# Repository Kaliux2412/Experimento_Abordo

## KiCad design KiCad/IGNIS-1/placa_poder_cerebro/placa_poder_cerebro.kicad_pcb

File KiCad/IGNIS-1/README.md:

# IGNIS-1 — estructura KiCad

## Fuente canónica = `boards/`

El diseño real y la fabricación viven en **3 proyectos KiCad independientes**:

- `boards/cerebro/` — power + MCU (ESP32, buck-boost 3V3, batería/RBF/switch)
- `boards/sensores/` — sensores + boost 5V (BME280, MPU6050, MQ-135, GPS)
- `boards/rf/` — comms + storage (LoRa RFM95W, microSD)

Cada uno es `*.kicad_pro` con su `*.kicad_sch` + `*.kicad_pcb`. **Abrir cada proyecto por separado** para editar/rutear. Se conectan por backplane 2×10 (J40/J41/J42, pinout idéntico).

## `IGNIS-1.kicad_sch` = NO CANÓNICO

El jerárquico raíz (`IGNIS-1.kicad_sch` + `sheets/*.kicad_sch`) es solo **referencia integrada histórica** previa al split en 3 placas. **NO refleja** los cambios hechos después en `boards/`:

- footprints `*_HandSolder` (C/R/LED SMD),
- caps bulk polarizados THT (`C_Polarized`: C2, C10, C32, C4),
- eliminación de U1 (protección 1S incluida en la celda LiPo) + re-cableado de la batería.

No editar ni fabricar desde el jerárquico.

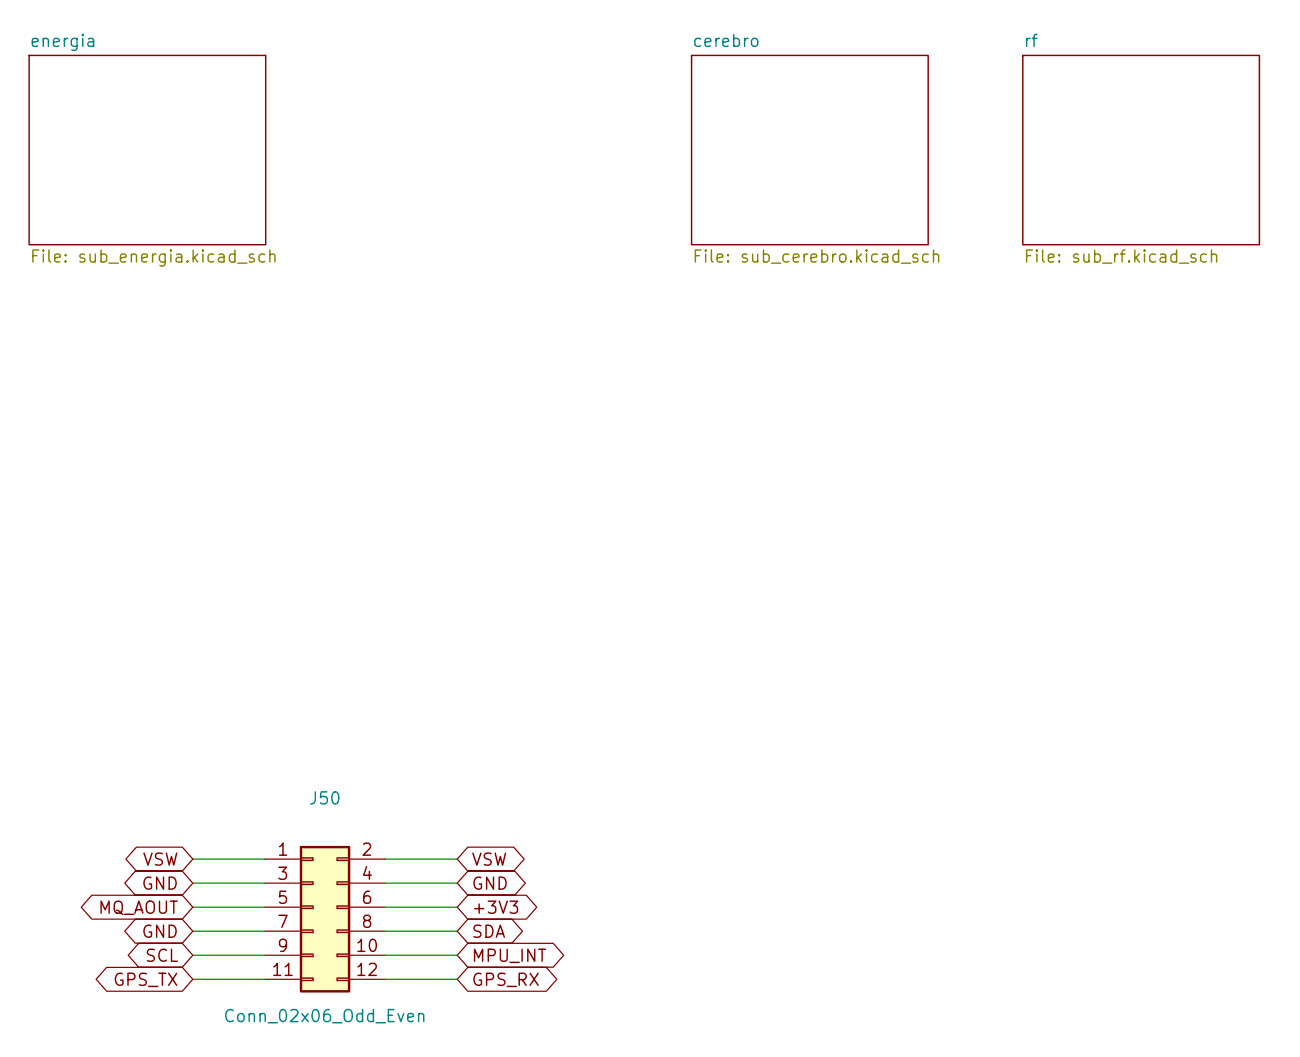
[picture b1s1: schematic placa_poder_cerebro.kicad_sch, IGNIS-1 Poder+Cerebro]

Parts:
J50: Conn_02x06_Odd_Even; PinHeader_2x06_P2.54mm_Vertical

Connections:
+3V3: J50.6; also elsewhere on the board
GND: J50.3, J50.4, J50.7; also elsewhere on the board
GPS_RX: J50.12; also elsewhere on the board
GPS_TX: J50.11; also elsewhere on the board
MPU_INT: J50.10; also elsewhere on the board
MQ_AOUT: J50.5; also elsewhere on the board
SCL: J50.9; also elsewhere on the board
SDA: J50.8; also elsewhere on the board
VSW: J50.1, J50.2; also elsewhere on the board

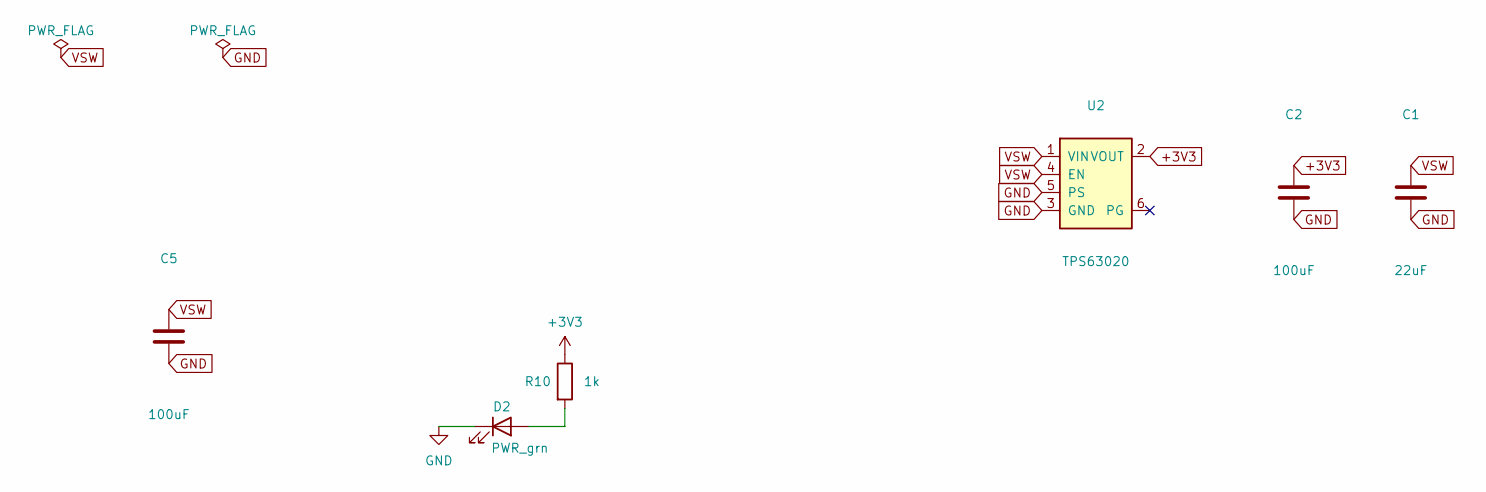
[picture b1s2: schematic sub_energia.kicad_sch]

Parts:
C1: 22uF; C_1206_3216Metric
C2, C5: 100uF; C_1210_3225Metric
D2: PWR_grn; LED_D3.0mm
R10: 1k; R_0805_2012Metric
U2: TPS63020; TPS63020_module

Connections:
+3V3: C2.1, R10.1, U2.2 (VOUT); also elsewhere on the board
GND: C1.2, C2.2, C5.2, D2.1 (K), U2.3 (GND), U2.5 (PS); also elsewhere on the board
unnamed: D2.2 (A), R10.2
VSW: C1.1, C5.1, U2.1 (VIN), U2.4 (EN); also elsewhere on the board

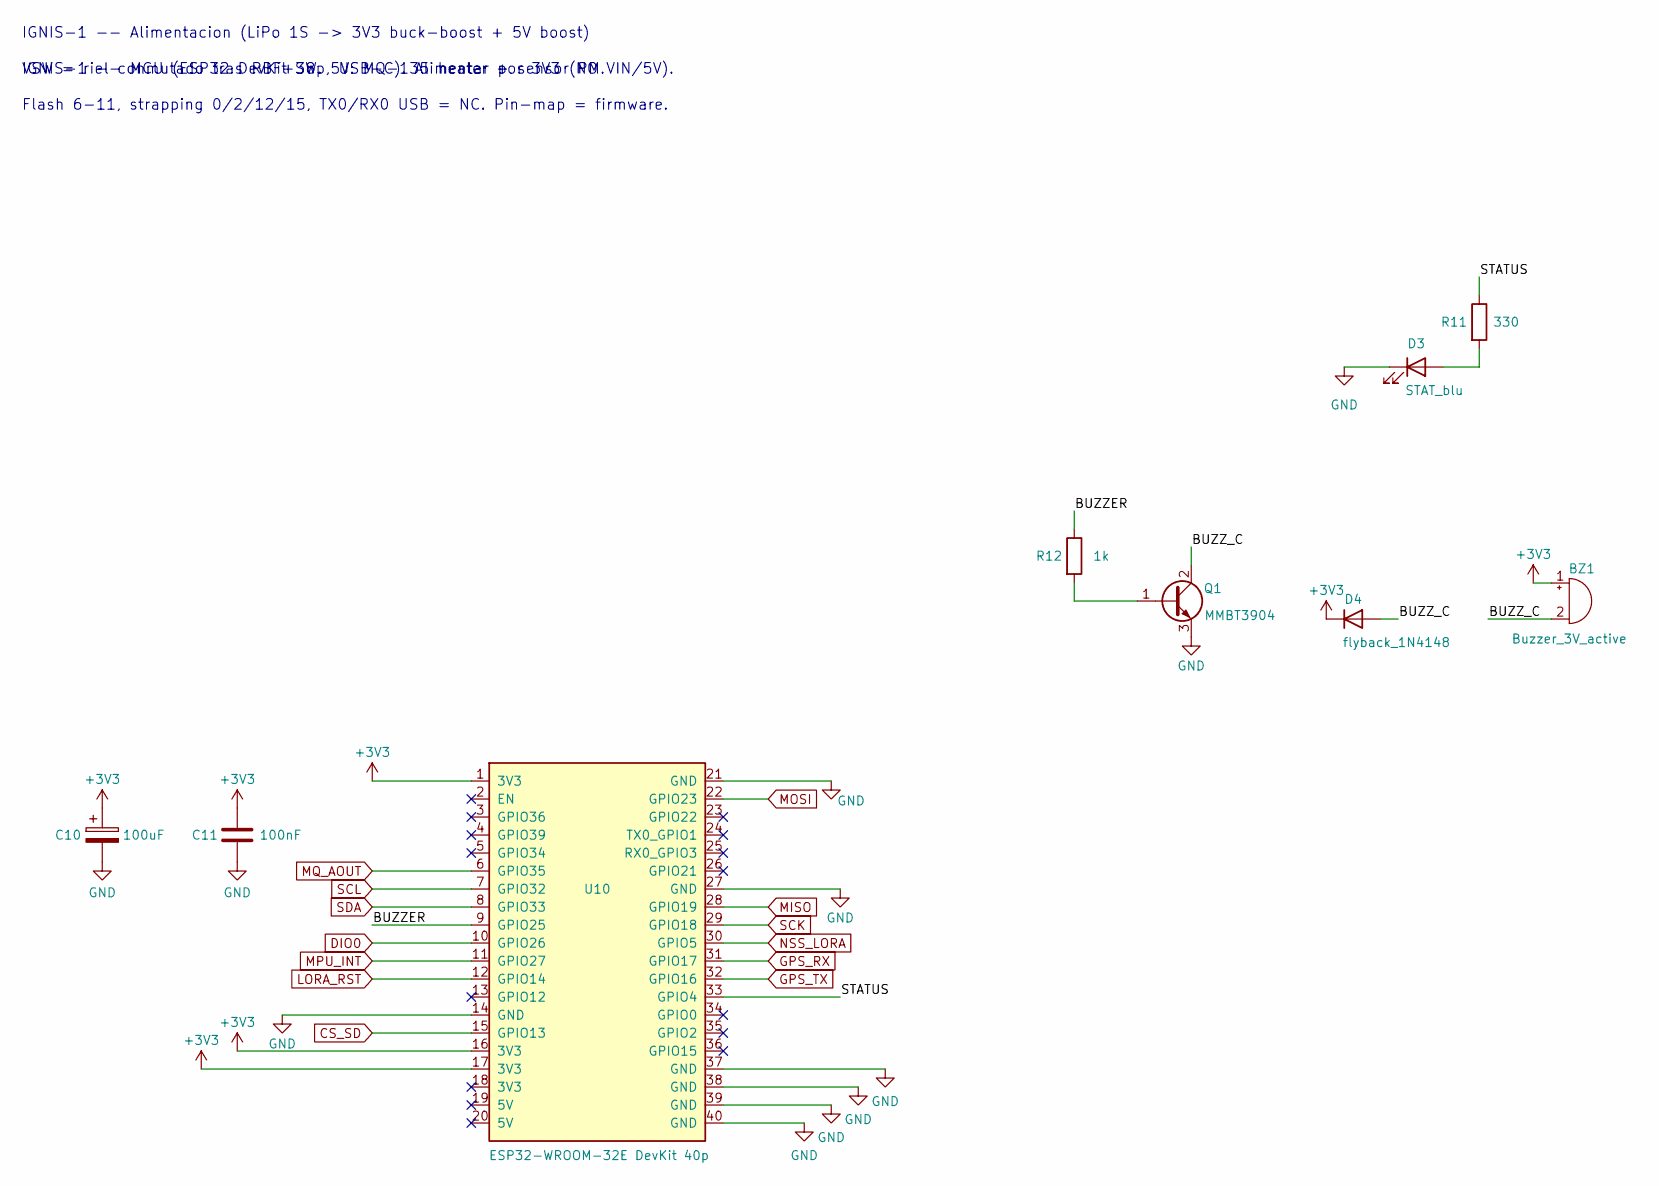
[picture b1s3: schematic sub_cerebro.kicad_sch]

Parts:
BZ1: Buzzer_3V_active; Buzzer_D12_P8.41
C10: 100uF; C_1210_3225Metric
C11: 100nF; C_0805_2012Metric
D3: STAT_blu; LED_D3.0mm
D4: flyback_1N4148; D_DO-35_SOD27_P7.62mm_Horizontal
Q1: MMBT3904; Q_TO92_2N3904_EBC
R11: 330; R_0805_2012Metric
R12: 1k; R_0805_2012Metric
U10: ESP32-WROOM-32E DevKit 40p; ESP32_DevKit_40p

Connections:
+3V3: BZ1.1 (+), C10.1, C11.1, D4.1 (K), U10.1 (3V3), U10.16 (3V3), U10.17 (3V3); also elsewhere on the board
/cerebro/BUZZER: R12.1, U10.9 (GPIO25)
/cerebro/BUZZ_C: BZ1.2 (-), D4.2 (A), Q1.2 (C)
/cerebro/STATUS: R11.1, U10.33 (GPIO4)
CS_SD: U10.15 (GPIO13); also elsewhere on the board
DIO0: U10.10 (GPIO26); also elsewhere on the board
GND: C10.2, C11.2, D3.1 (K), Q1.3 (E), U10.14 (GND), U10.21 (GND), U10.27 (GND), U10.37 (GND), U10.38 (GND), U10.39 (GND), U10.40 (GND); also elsewhere on the board
GPS_RX: U10.31 (GPIO17); also elsewhere on the board
GPS_TX: U10.32 (GPIO16); also elsewhere on the board
LORA_RST: U10.12 (GPIO14); also elsewhere on the board
MISO: U10.28 (GPIO19); also elsewhere on the board
MOSI: U10.22 (GPIO23); also elsewhere on the board
MPU_INT: U10.11 (GPIO27); also elsewhere on the board
MQ_AOUT: U10.6 (GPIO35); also elsewhere on the board
NSS_LORA: U10.30 (GPIO5); also elsewhere on the board
unnamed: D3.2 (A), R11.2
unnamed: Q1.1 (B), R12.2
SCK: U10.29 (GPIO18); also elsewhere on the board
SCL: U10.7 (GPIO32); also elsewhere on the board
SDA: U10.8 (GPIO33); also elsewhere on the board

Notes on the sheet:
VSW = riel conmutado tras RBF+SW. 5V: MQ-135 heater + sensor PM.
Flash 6-11, strapping 0/2/12/15, TX0/RX0 USB = NC. Pin-map = firmware.
IGNIS-1 -- Alimentacion (LiPo 1S -> 3V3 buck-boost + 5V boost)
IGNIS-1 -- MCU (ESP32 DevKit 38p, USB-C). Alimentar por 3V3 (NO VIN/5V).

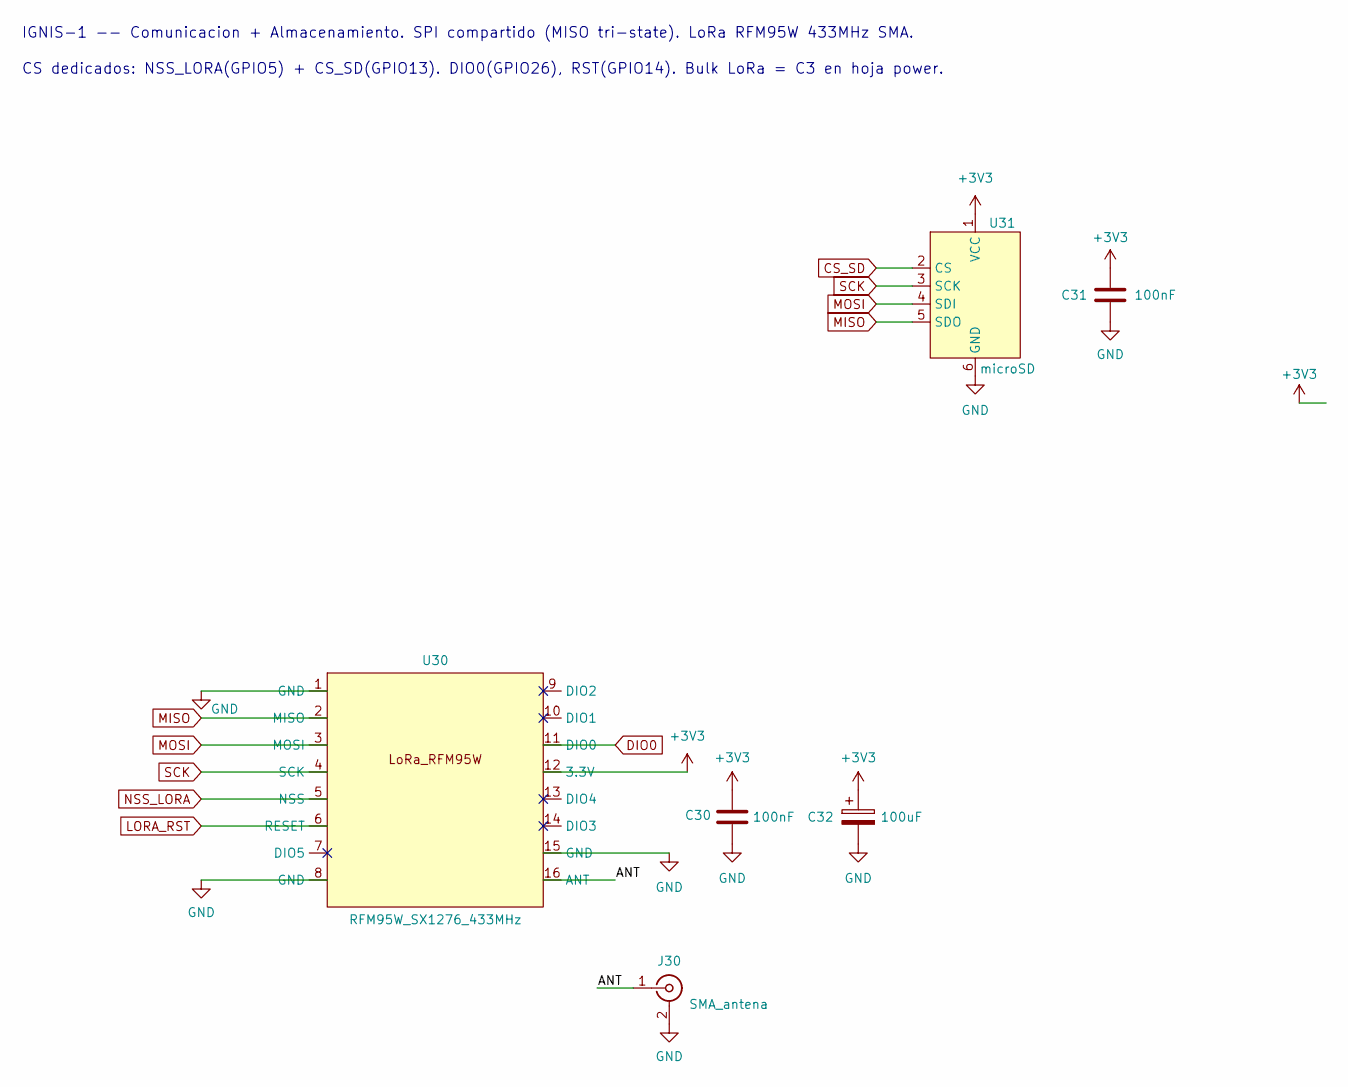
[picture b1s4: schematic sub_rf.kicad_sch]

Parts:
C30, C31: 100nF; C_0805_2012Metric
C32: 100uF; C_1210_3225Metric
J30: SMA_antena; SMA_Amphenol_901-144_Vertical
U30: RFM95W_SX1276_433MHz; LoRa_RFM95_adapter
U31: microSD; MicroSD_module

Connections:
+3V3: C30.1, C31.1, C32.1, U30.12 (3.3V), U31.1 (VCC); also elsewhere on the board
/rf/ANT: J30.1 (In), U30.16 (ANT)
CS_SD: U31.2 (CS); also elsewhere on the board
DIO0: U30.11 (DIO0); also elsewhere on the board
GND: C30.2, C31.2, C32.2, J30.2 (Ext), U30.1 (GND), U30.8 (GND), U30.15 (GND), U31.6 (GND); also elsewhere on the board
LORA_RST: U30.6 (RESET); also elsewhere on the board
MISO: U30.2 (MISO), U31.5 (SDO); also elsewhere on the board
MOSI: U30.3 (MOSI), U31.4 (SDI); also elsewhere on the board
NSS_LORA: U30.5 (NSS); also elsewhere on the board
SCK: U30.4 (SCK), U31.3 (SCK); also elsewhere on the board

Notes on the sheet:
IGNIS-1 -- Comunicacion + Almacenamiento. SPI compartido (MISO tri-state). LoRa RFM95W 433MHz SMA.
CS dedicados: NSS_LORA(GPIO5) + CS_SD(GPIO13). DIO0(GPIO26), RST(GPIO14). Bulk LoRa = C3 en hoja power.

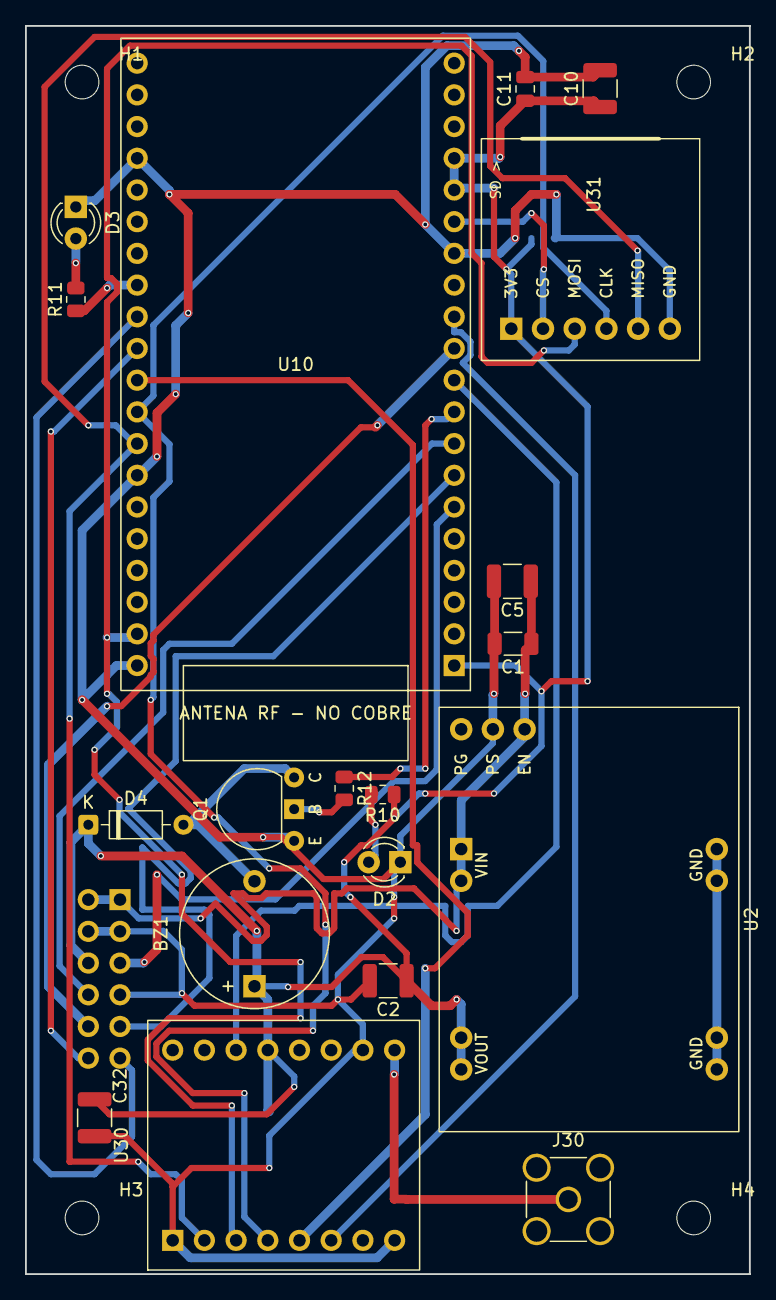
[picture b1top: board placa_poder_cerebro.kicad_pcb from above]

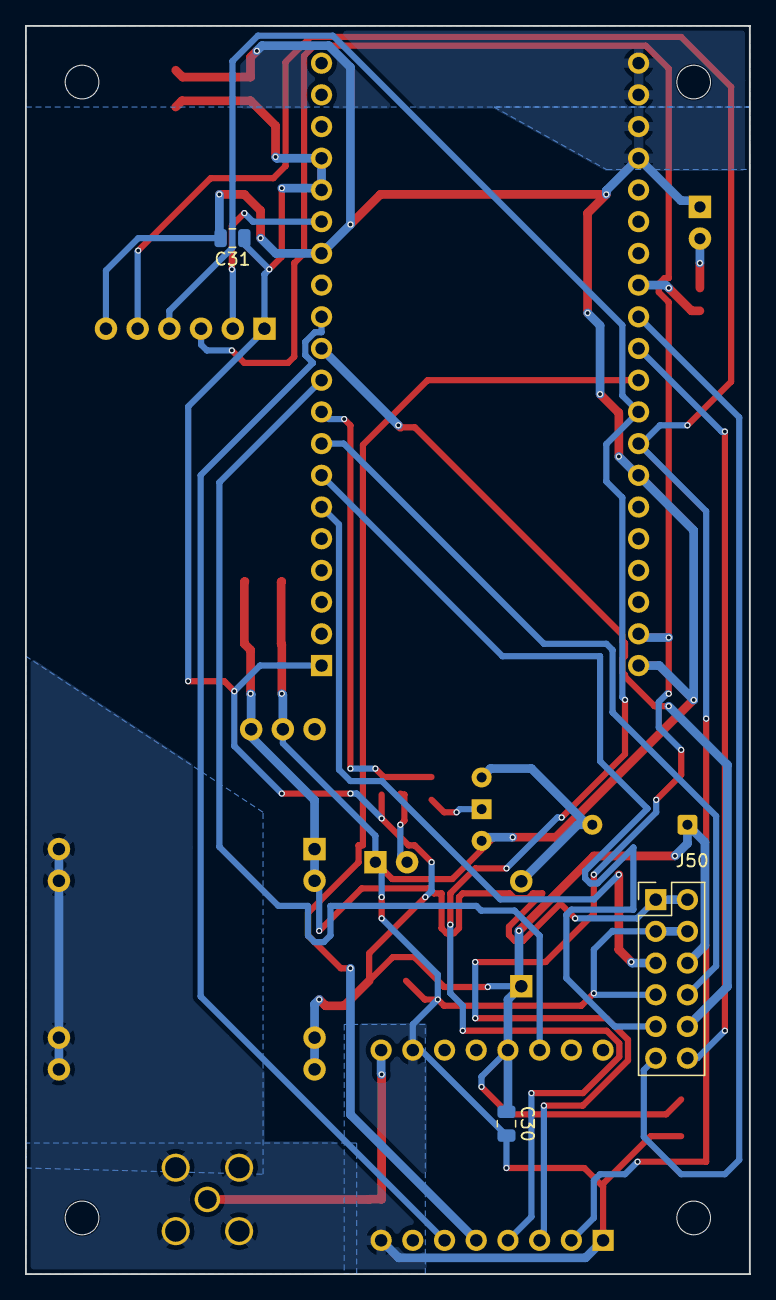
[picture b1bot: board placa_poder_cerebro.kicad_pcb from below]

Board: 2 copper layers, 58.0 x 100.0 mm, 26 parts (3 on the bottom side), 23 nets.

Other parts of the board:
H1, H2, H3, H4: M2.5_hole; MountingHole_2.7mm_M2.5

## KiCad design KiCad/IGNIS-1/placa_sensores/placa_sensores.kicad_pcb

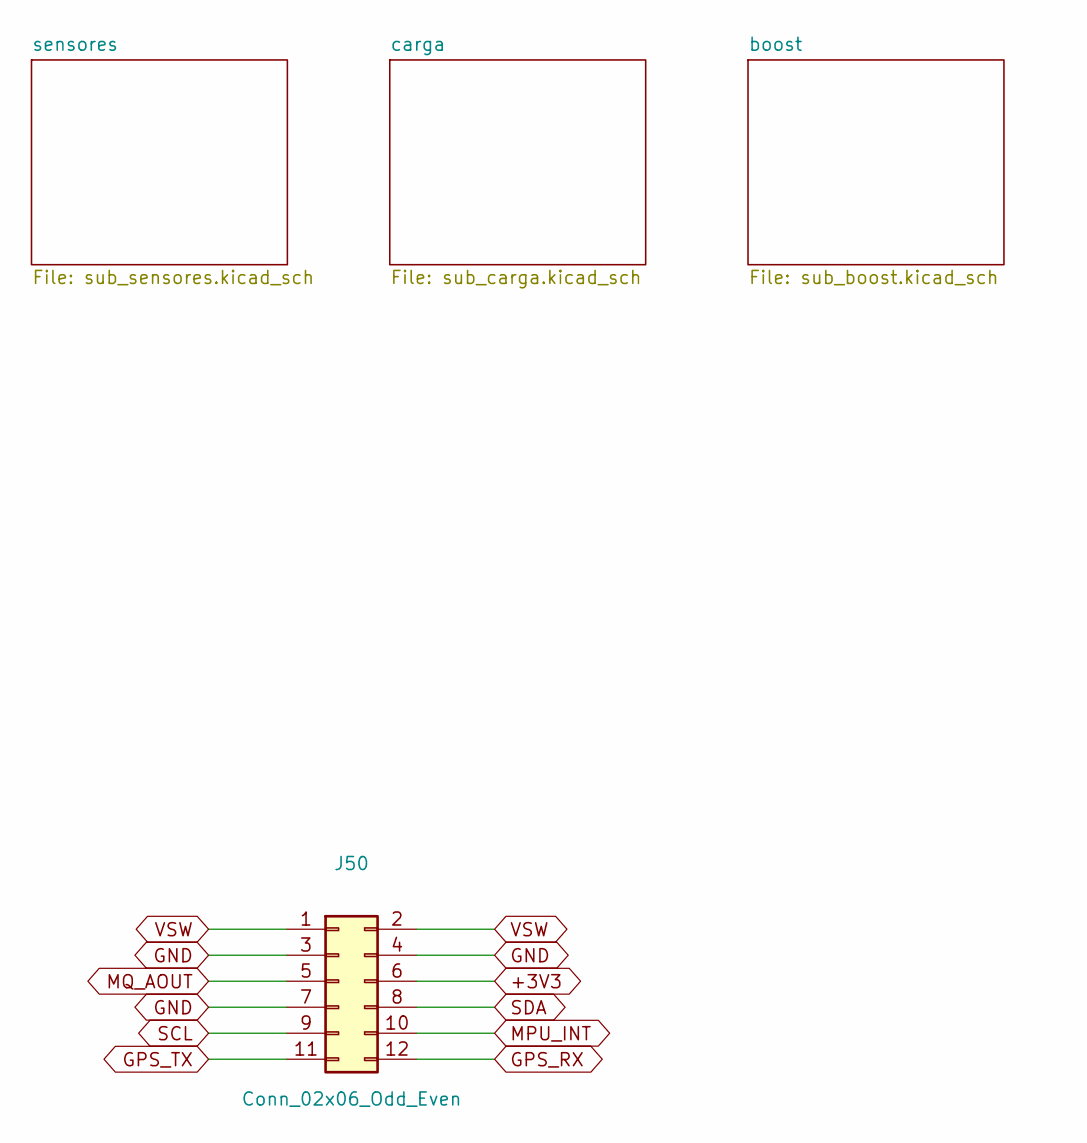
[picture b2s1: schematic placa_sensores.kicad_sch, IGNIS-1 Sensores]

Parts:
J50: Conn_02x06_Odd_Even; PinSocket_2x06_P2.54mm_Vertical

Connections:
+3V3: J50.6; also elsewhere on the board
GND: J50.3, J50.4, J50.7; also elsewhere on the board
GPS_RX: J50.12; also elsewhere on the board
GPS_TX: J50.11; also elsewhere on the board
MPU_INT: J50.10; also elsewhere on the board
MQ_AOUT: J50.5; also elsewhere on the board
SCL: J50.9; also elsewhere on the board
SDA: J50.8; also elsewhere on the board
VSW: J50.1, J50.2; also elsewhere on the board

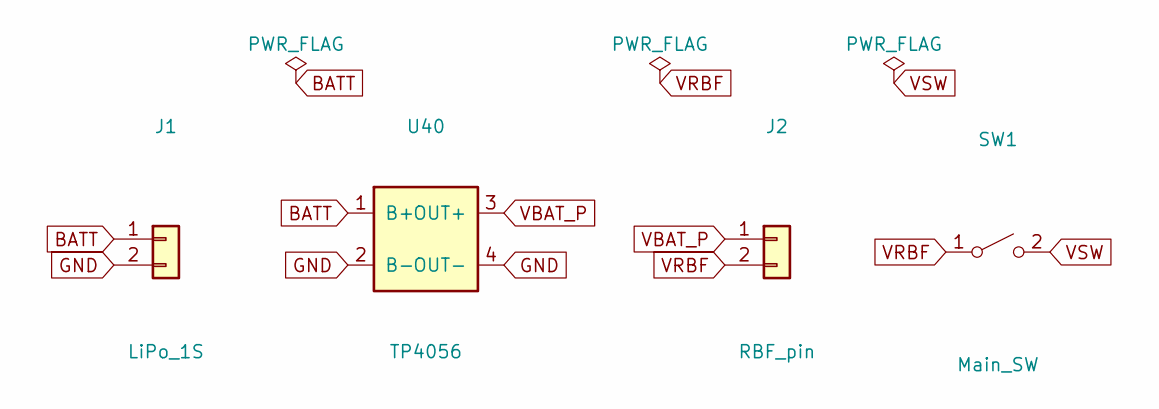
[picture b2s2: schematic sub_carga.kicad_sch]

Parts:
J1: LiPo_1S; JST_PH_B2B-PH-K_1x02_P2.00mm_Vertical
J2: RBF_pin; PinHeader_1x02_P2.54mm_Vertical
SW1: Main_SW; SW_Slide_SS12D00
U40: TP4056; TP4056_HW373_module

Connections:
BATT: J1.1, U40.1 (B+)
GND: J1.2, U40.2 (B-), U40.4 (OUT-); also elsewhere on the board
VBAT_P: J2.1, U40.3 (OUT+)
VRBF: J2.2, SW1.1 (A)
VSW: SW1.2 (B); also elsewhere on the board

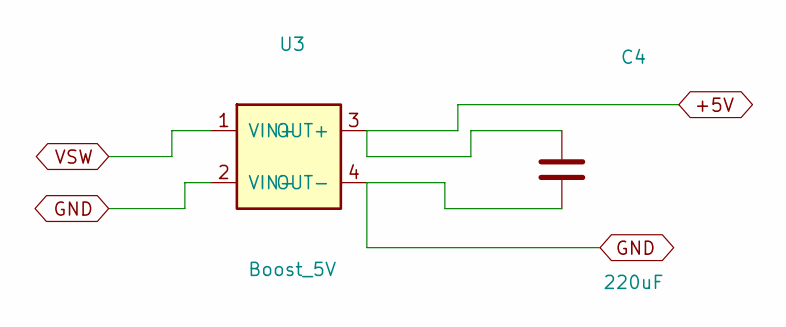
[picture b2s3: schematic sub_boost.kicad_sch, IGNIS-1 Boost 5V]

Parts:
C4: 220uF; CP_EIA-7343-31_Kemet-D
U3: Boost_5V; MT3608_module

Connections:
+5V: C4.1, U3.3 (OUT+); also elsewhere on the board
GND: C4.2, U3.2 (VIN-), U3.4 (OUT-); also elsewhere on the board
VSW: U3.1 (VIN+); also elsewhere on the board

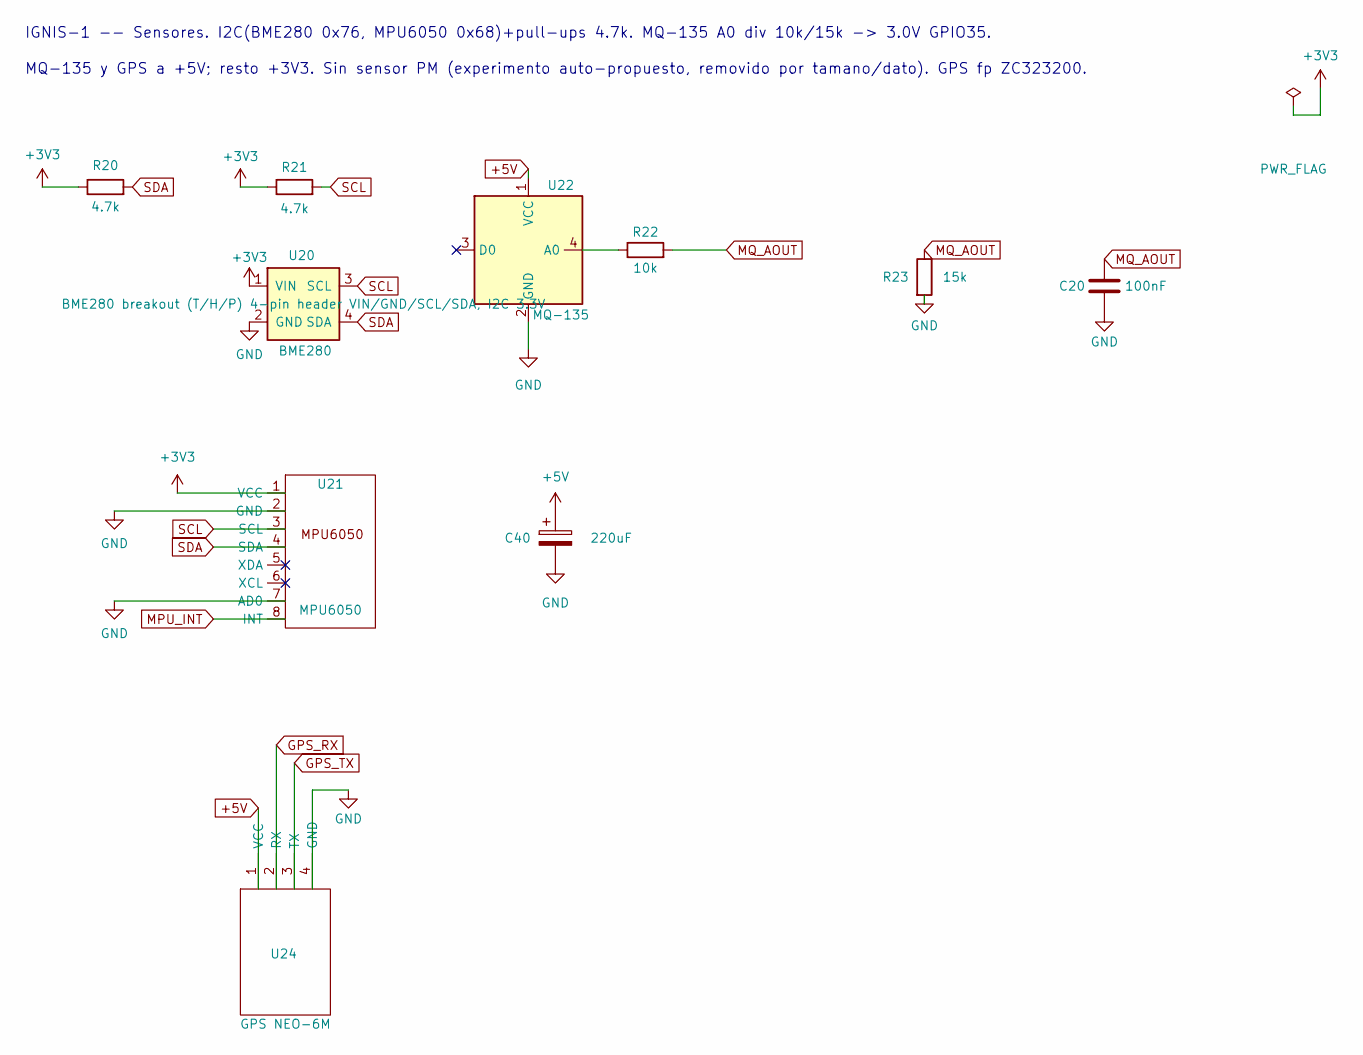
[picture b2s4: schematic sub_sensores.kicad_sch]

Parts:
C20: 100nF; C_0805_2012Metric
C40: 220uF; CP_EIA-7343-31_Kemet-D
R20, R21: 4.7k; R_0805_2012Metric
R22: 10k; R_0805_2012Metric
R23: 15k; R_0805_2012Metric
U20: BME280; BME280_module
U21: MPU6050; MPU6050_module
U22: MQ-135; PinHeader_1x04_P2.54mm_Vertical
U24: GPS NEO-6M; GPS_NEO6M_module

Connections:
+3V3: R20.1, R21.1, U20.1 (VIN), U21.1 (VCC); also elsewhere on the board
+5V: C40.1, U22.1 (VCC), U24.1 (VCC); also elsewhere on the board
GND: C20.2, C40.2, R23.2, U20.2 (GND), U21.2 (GND), U21.7 (AD0), U22.2 (GND), U24.4 (GND); also elsewhere on the board
GPS_RX: U24.2 (RX); also elsewhere on the board
GPS_TX: U24.3 (TX); also elsewhere on the board
MPU_INT: U21.8 (INT); also elsewhere on the board
MQ_AOUT: C20.1, R22.2, R23.1; also elsewhere on the board
unnamed: R22.1, U22.4 (A0)
SCL: R21.2, U20.3 (SCL), U21.3 (SCL); also elsewhere on the board
SDA: R20.2, U20.4 (SDA), U21.4 (SDA); also elsewhere on the board

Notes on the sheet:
IGNIS-1 -- Sensores. I2C(BME280 0x76, MPU6050 0x68)+pull-ups 4.7k. MQ-135 A0 div 10k/15k -> 3.0V GPIO35.
MQ-135 y GPS a +5V; resto +3V3. Sin sensor PM (experimento auto-propuesto, removido por tamano/dato). GPS fp ZC323200.

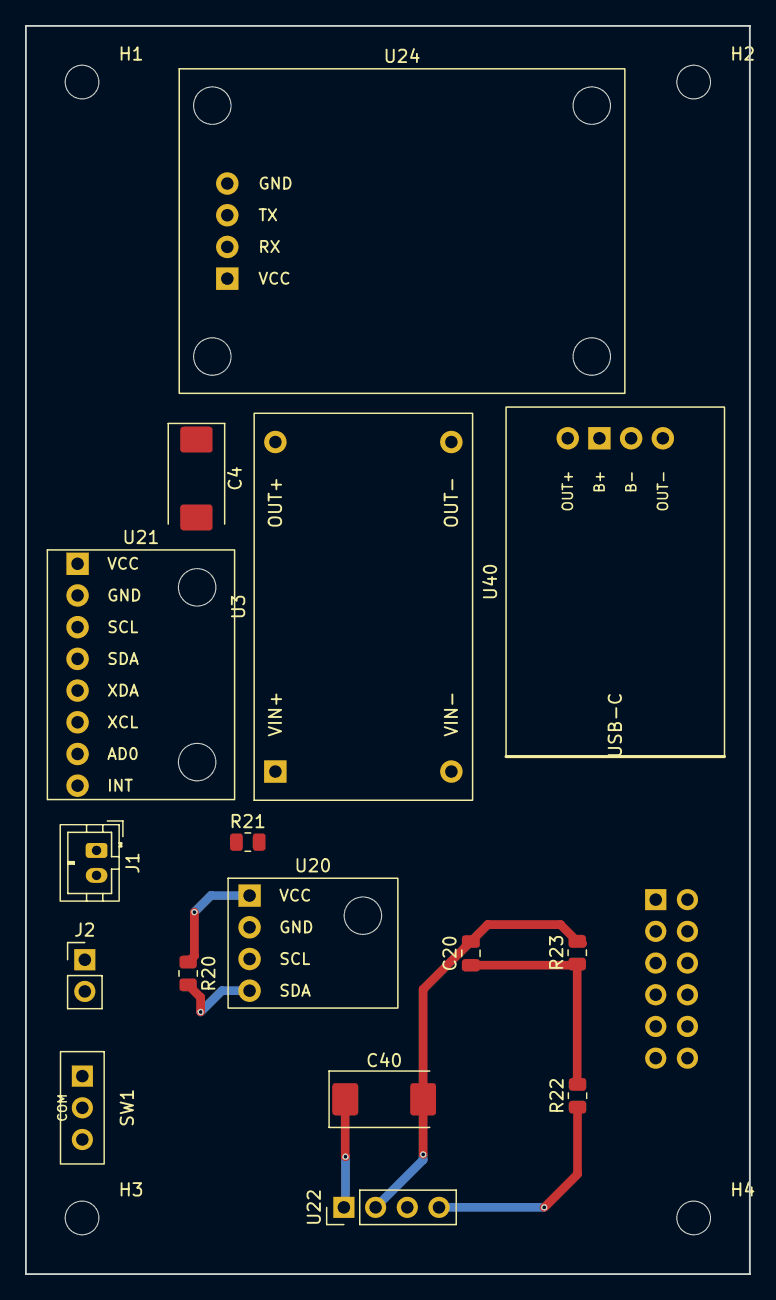
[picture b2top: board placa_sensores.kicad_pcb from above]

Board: 2 copper layers, 58.0 x 100.0 mm, 21 parts (1 on the bottom side), 14 nets.

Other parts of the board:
H1, H2, H3, H4: M2.5_hole; MountingHole_2.7mm_M2.5

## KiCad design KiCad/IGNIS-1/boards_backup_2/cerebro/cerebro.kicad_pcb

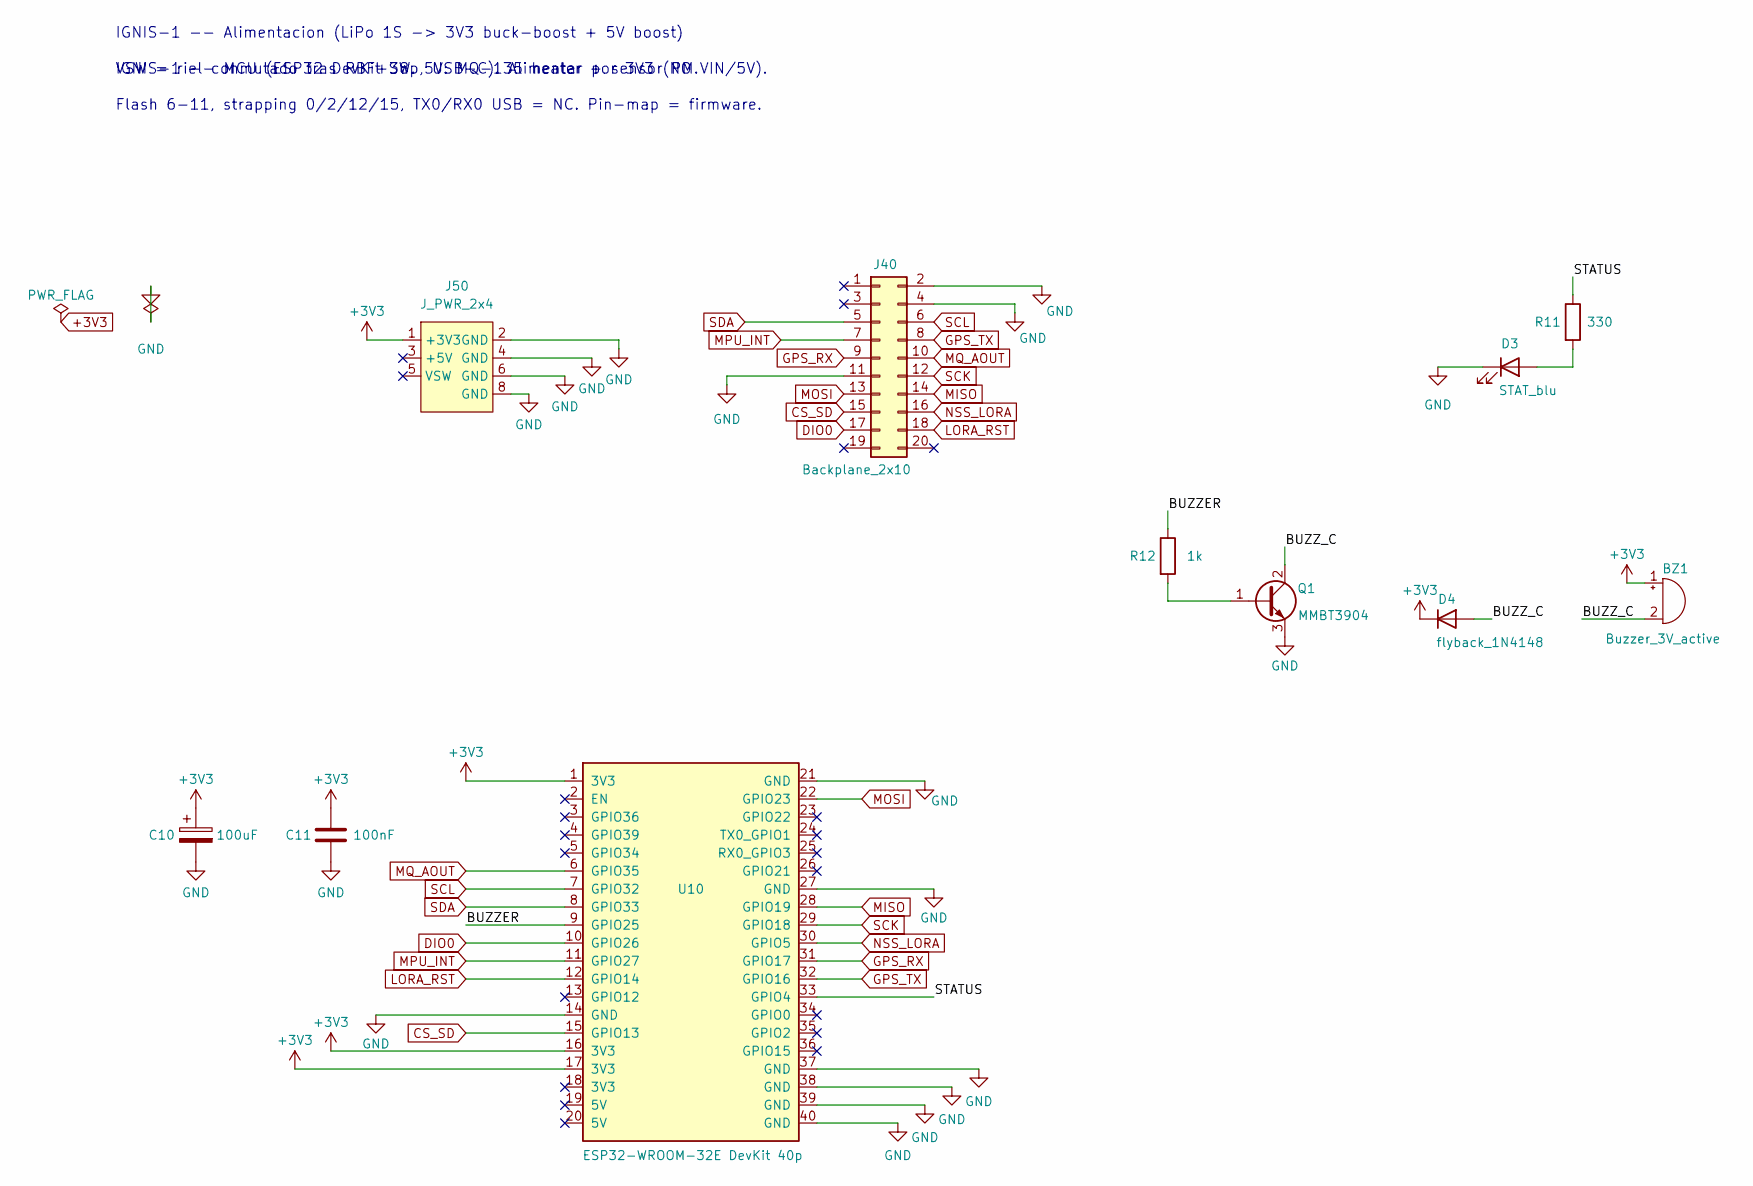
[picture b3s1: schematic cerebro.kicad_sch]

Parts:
BZ1: Buzzer_3V_active; Buzzer_D12_P8.41
C10: 100uF; CP_Radial_D8.0mm_P3.80mm
C11: 100nF; C_Disc_D7.5mm_W2.5mm_P5.00mm
D3: STAT_blu; LED_D3.0mm
D4: flyback_1N4148; D_DO-35_SOD27_P7.62mm_Horizontal
J40: Backplane_2x10; PinHeader_2x10_P2.54mm_Vertical
J50: J_PWR_2x4; J_PWR_2x4_Keyed
Q1: MMBT3904; Q_TO92_2N3904_EBC
R11: 330; R_Axial_DIN0207_L6.3mm_D2.5mm_P7.62mm_Horizontal
R12: 1k; R_Axial_DIN0207_L6.3mm_D2.5mm_P7.62mm_Horizontal
U10: ESP32-WROOM-32E DevKit 40p; ESP32_DevKit_40p

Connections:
+3V3: BZ1.1 (+), C10.1, C11.1, D4.1 (K), J50.1 (+3V3), U10.1 (3V3), U10.16 (3V3), U10.17 (3V3)
/BUZZER: R12.1, U10.9 (GPIO25)
/BUZZ_C: BZ1.2 (-), D4.2 (A), Q1.2 (C)
/STATUS: R11.1, U10.33 (GPIO4)
CS_SD: J40.15, U10.15 (GPIO13)
DIO0: J40.17, U10.10 (GPIO26)
GND: C10.2, C11.2, D3.1 (K), J40.2, J40.4, J40.11, J50.2 (GND), J50.4 (GND), J50.6 (GND), J50.8 (GND), Q1.3 (E), U10.14 (GND), U10.21 (GND), U10.27 (GND), U10.37 (GND), U10.38 (GND), U10.39 (GND), U10.40 (GND)
GPS_RX: J40.9, U10.31 (GPIO17)
GPS_TX: J40.8, U10.32 (GPIO16)
LORA_RST: J40.18, U10.12 (GPIO14)
MISO: J40.14, U10.28 (GPIO19)
MOSI: J40.13, U10.22 (GPIO23)
MPU_INT: J40.7, U10.11 (GPIO27)
MQ_AOUT: J40.10, U10.6 (GPIO35)
NSS_LORA: J40.16, U10.30 (GPIO5)
unnamed: D3.2 (A), R11.2
unnamed: Q1.1 (B), R12.2
SCK: J40.12, U10.29 (GPIO18)
SCL: J40.6, U10.7 (GPIO32)
SDA: J40.5, U10.8 (GPIO33)

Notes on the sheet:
VSW = riel conmutado tras RBF+SW. 5V: MQ-135 heater + sensor PM.
Flash 6-11, strapping 0/2/12/15, TX0/RX0 USB = NC. Pin-map = firmware.
IGNIS-1 -- Alimentacion (LiPo 1S -> 3V3 buck-boost + 5V boost)
IGNIS-1 -- MCU (ESP32 DevKit 38p, USB-C). Alimentar por 3V3 (NO VIN/5V).

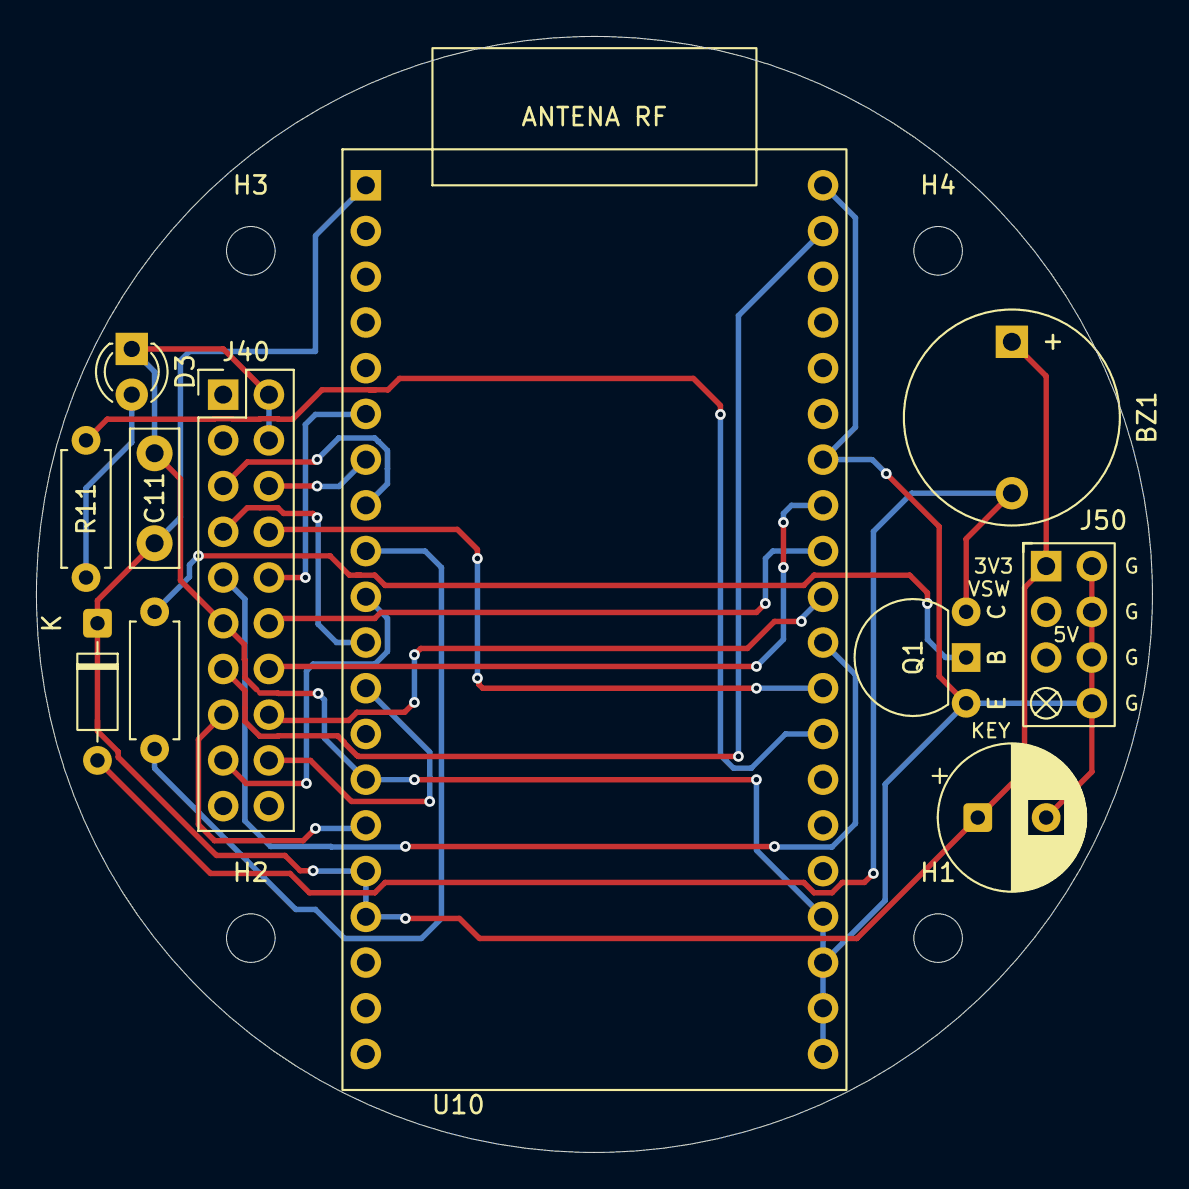
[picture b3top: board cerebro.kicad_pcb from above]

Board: 2 copper layers, 62.0 x 62.0 mm, 15 parts (0 on the bottom side), 20 nets.

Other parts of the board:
H1, H2, H3, H4: M2.5_hole; MountingHole_2.7mm_M2.5

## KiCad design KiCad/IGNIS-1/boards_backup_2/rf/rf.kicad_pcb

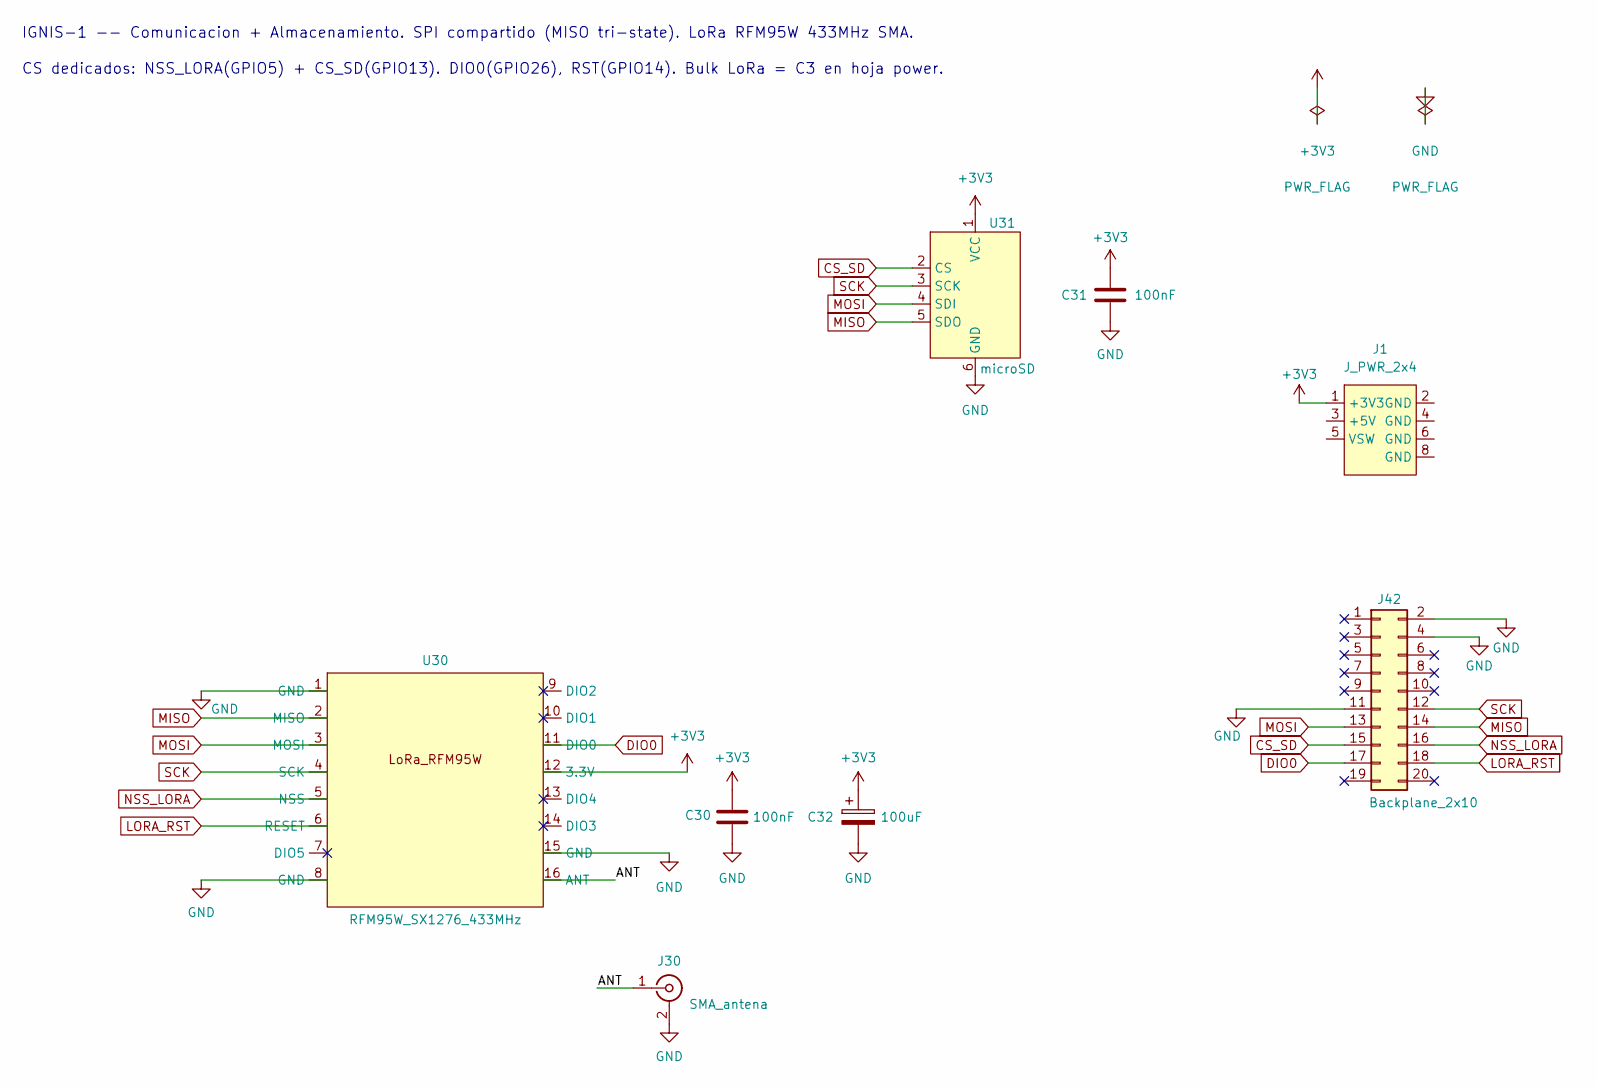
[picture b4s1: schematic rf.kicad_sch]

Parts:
C30, C31: 100nF; C_Disc_D7.5mm_W2.5mm_P5.00mm
C32: 100uF; CP_Radial_D8.0mm_P3.80mm
J1: J_PWR_2x4; J_PWR_2x4_Keyed
J30: SMA_antena; SMA_Amphenol_901-144_Vertical
J42: Backplane_2x10; PinHeader_2x10_P2.54mm_Vertical
U30: RFM95W_SX1276_433MHz; LoRa_RFM95_adapter
U31: microSD; PinHeader_1x06_P2.54mm_Vertical

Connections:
+3V3: C30.1, C31.1, C32.1, J1.1 (+3V3_1), U30.12 (3.3V), U31.1 (VCC)
/ANT: J30.1 (In), U30.16 (ANT)
CS_SD: J42.15, U31.2 (CS)
DIO0: J42.17, U30.11 (DIO0)
GND: C30.2, C31.2, C32.2, J30.2 (Ext), J42.2, J42.4, J42.11, U30.1 (GND), U30.8 (GND), U30.15 (GND), U31.6 (GND)
LORA_RST: J42.18, U30.6 (RESET)
MISO: J42.14, U30.2 (MISO), U31.5 (SDO)
MOSI: J42.13, U30.3 (MOSI), U31.4 (SDI)
NSS_LORA: J42.16, U30.5 (NSS)
SCK: J42.12, U30.4 (SCK), U31.3 (SCK)

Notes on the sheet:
IGNIS-1 -- Comunicacion + Almacenamiento. SPI compartido (MISO tri-state). LoRa RFM95W 433MHz SMA.
CS dedicados: NSS_LORA(GPIO5) + CS_SD(GPIO13). DIO0(GPIO26), RST(GPIO14). Bulk LoRa = C3 en hoja power.
